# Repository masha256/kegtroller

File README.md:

kegtroller
==========

Arduino-based RFID/NFC kegerator controller with wi-fi and backend API integrated with paypal

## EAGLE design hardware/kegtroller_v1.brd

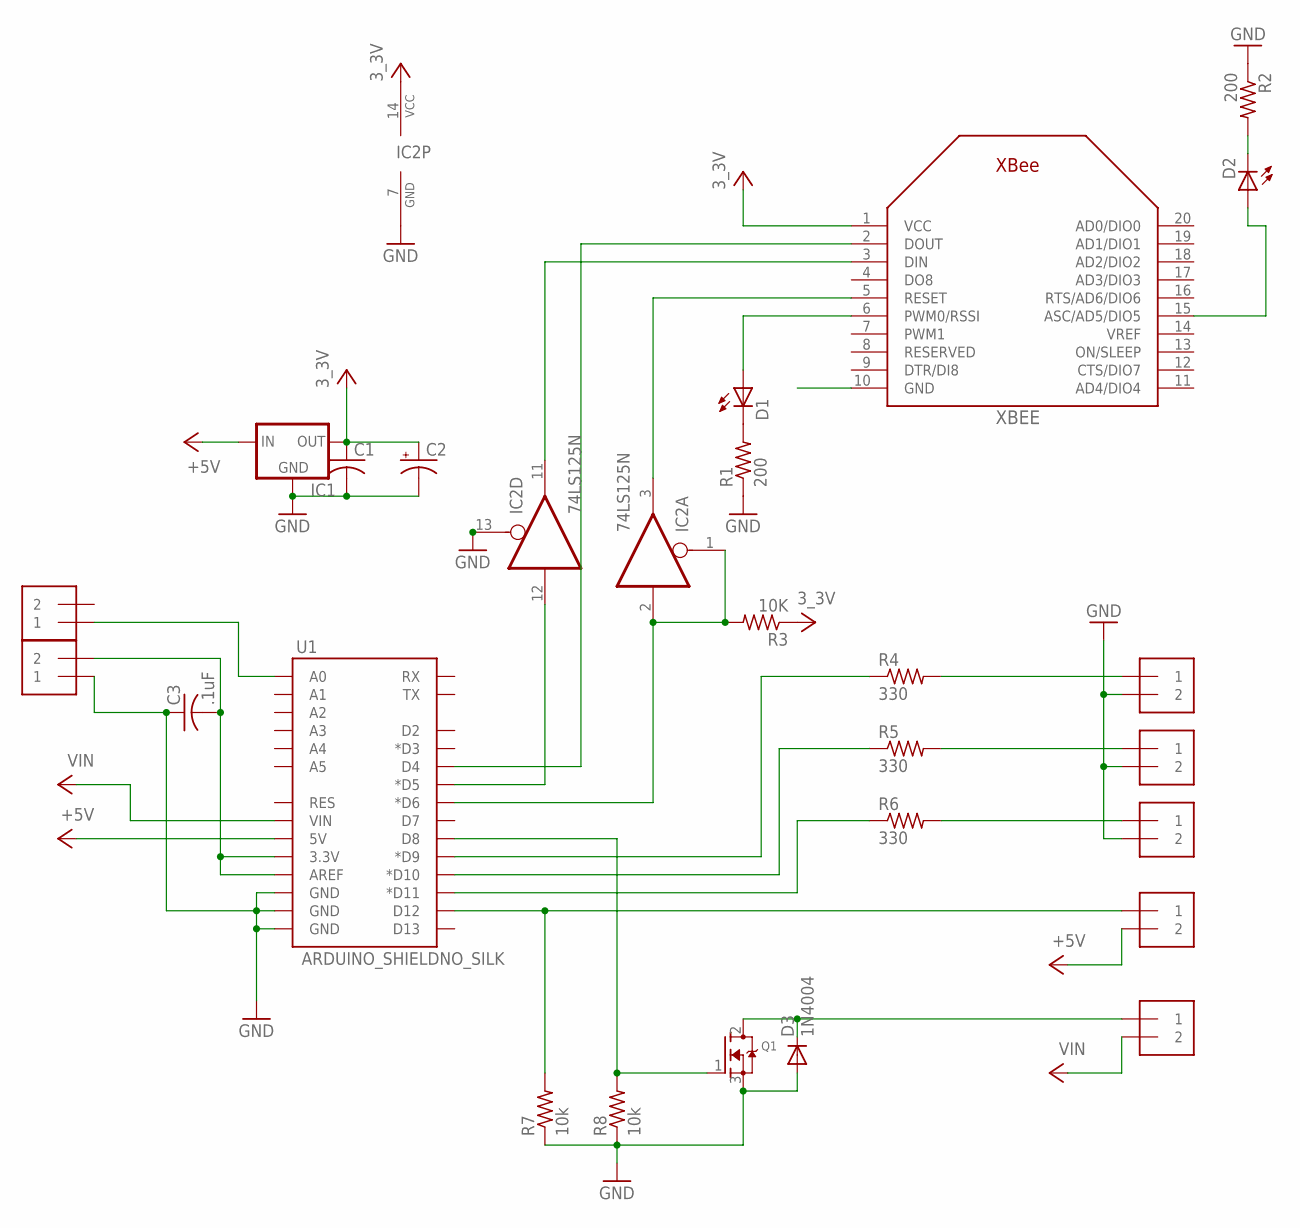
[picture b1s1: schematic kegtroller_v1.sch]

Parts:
C1: C-US025-025X050; C025-025X050
C2: CPOL-USE2.5-5; E2,5-5
C3: .1uF; C025-025X050
D1, D2: LED3MM
D3: 1N4004; DO41-10
IC1: MC1700; TO92
IC2: 74LS125N; DIL14
J1, J2, J3, J4, J5, J6, J7: 1X2-3.5MM
Q1: MOSFET-NGDS_TO220V; TO220V
R1, R2: 200; 0207/10
R3: 10K; 0207/10
R4, R5, R6: 330; 0204/5
R7, R8: 10k; 0204/5
U1: ARDUINO_SHIELDNO_SILK; DUEMILANOVE_VIAS
XBEE: XBEE

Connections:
3_3V: C1.1, C2.+, IC1.3 (OUT), IC2.14 (VCC), R3.1, XBEE.1 (VCC)
+5V: IC1.2 (IN), J4.2, U1.5V
GND: C1.2, C2.-, C3.1, D3.A, IC1.1 (GND), IC2.7 (GND), IC2.13 (OE), J1.2, J2.2, J3.2, J6.1, Q1.3 (S), R1.1, R2.1, R7.1, R8.1, U1.GND@0 (GND), U1.GND@1 (GND), U1.GND@2 (GND), XBEE.10 (GND)
unnamed: IC2.12 (I), U1.D5 (*D5)
unnamed: IC2.11 (O), XBEE.3 (DIN)
unnamed: D2.K (C), R2.2
unnamed: D1.A, XBEE.6 (PWM0/RSSI)
unnamed: D1.K (C), R1.2
unnamed: D2.A, XBEE.15 (ASC/AD5/DIO5)
unnamed: IC2.3 (O), XBEE.5 (RESET)
unnamed: R4.1, U1.D9 (*D9)
unnamed: R5.1, U1.D10 (*D10)
unnamed: R6.1, U1.D11 (*D11)
unnamed: J1.1, R4.2
unnamed: J2.1, R5.2
unnamed: J3.1, R6.2
unnamed: C3.2, J6.2, U1.3.3V, U1.AREF
unnamed: J5.1, U1.A0
unnamed: J4.1, R7.2, U1.D12
unnamed: D3.C, J7.1, Q1.2 (D)
unnamed: Q1.1 (G), R8.2, U1.D8
RESET: IC2.1 (OE), IC2.2 (I), R3.2, U1.D6 (*D6)
TX: U1.D4, XBEE.2 (DOUT)
VIN: J7.2, U1.VIN

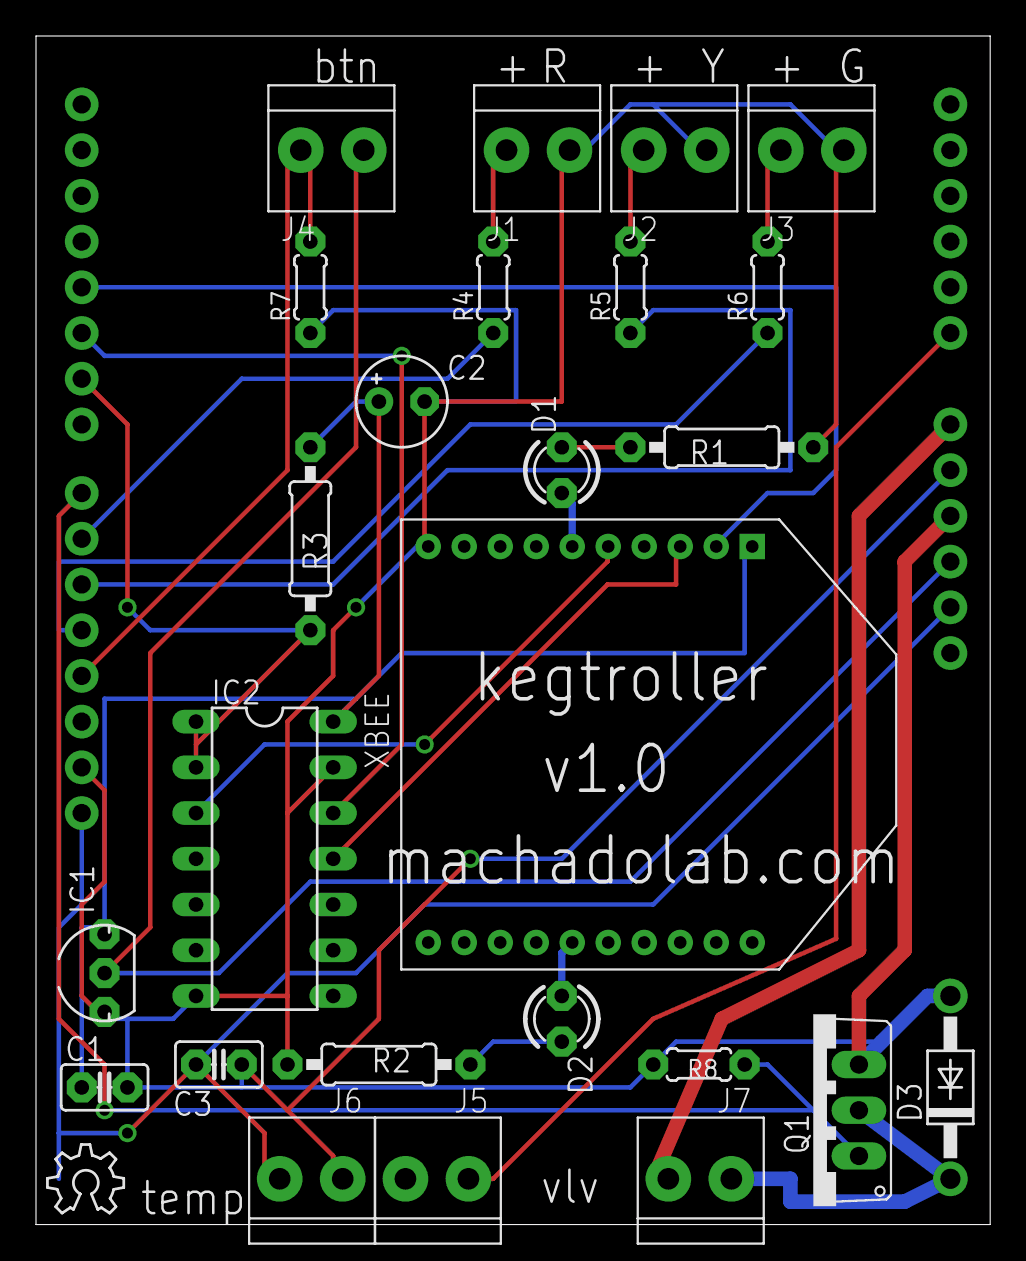
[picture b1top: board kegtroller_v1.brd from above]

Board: 2 copper layers, 53.0 x 66.0 mm, 28 parts (1 on the bottom side), 24 nets.

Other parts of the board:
U$1: OSHW_6X150_NOTEXT
U$2: OSHW_10X750_NOTEXT

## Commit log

2012-07-24 Added initial files
2012-07-24 Enabled code to control the valve

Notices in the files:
parts and their libraries:
SparkFun-Boards: Licensing: CC v3.0 Share-Alike You are welcome to use this library for commercial purposes.
